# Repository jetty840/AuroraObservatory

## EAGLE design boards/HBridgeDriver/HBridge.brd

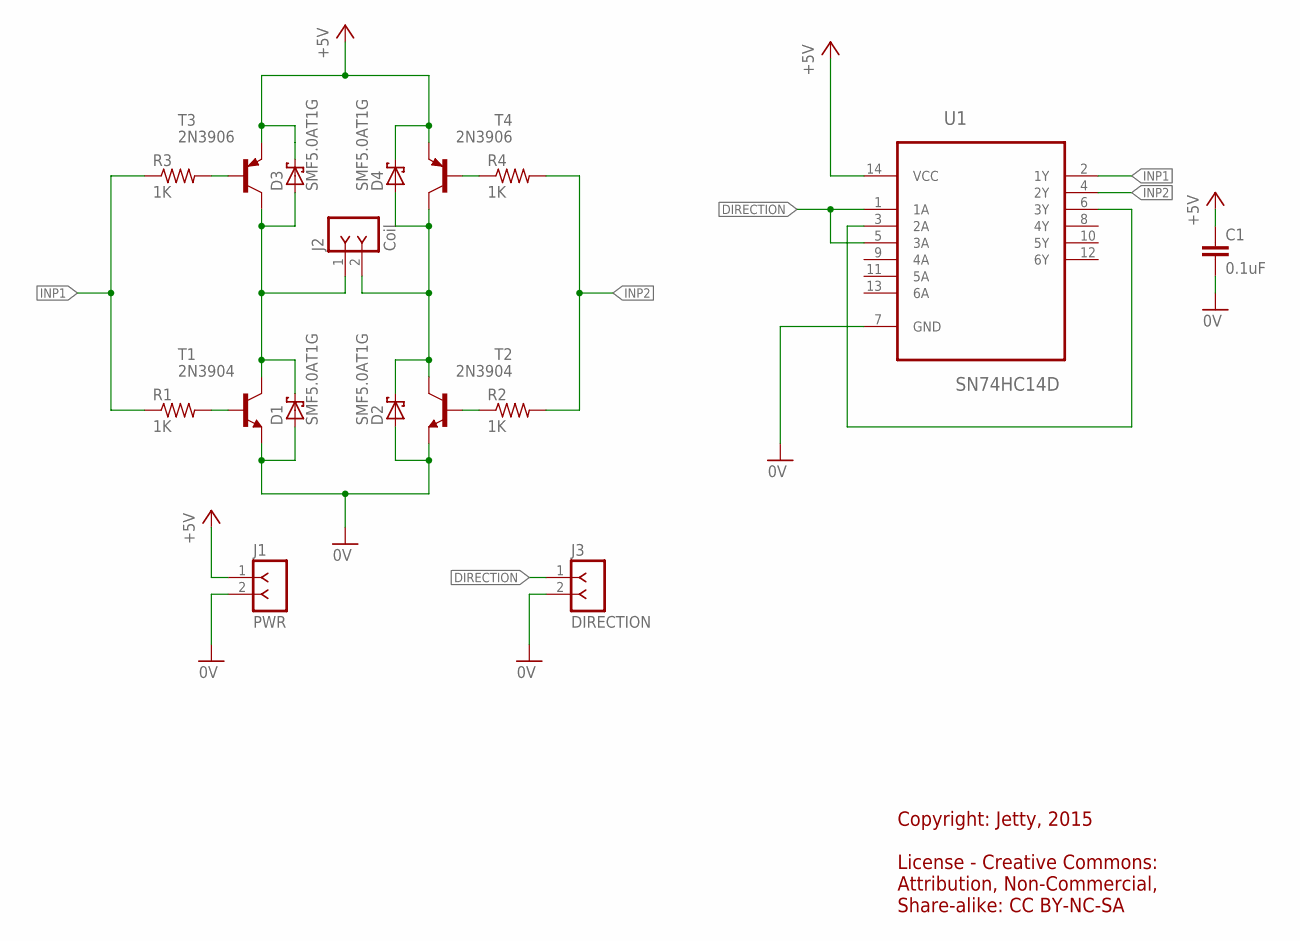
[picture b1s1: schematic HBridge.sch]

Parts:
C1: 0.1uF; C0603
D1, D2, D3, D4: SMF5.0AT1G; SOD123FL
J1: PWR; SIP-100-02-32Y
J2: Coil; SIP-100-02-32Y
J3: DIRECTION; SIP-100-02-32Y
R1, R2, R3, R4: 1K; R0603
T1, T2: 2N3904; SOT23-BEC
T3, T4: 2N3906; SOT23-BEC
U1: SN74HC14D; SOIC127P600X175-14N

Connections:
0V: C1.2, D1.A, D2.A, J1.2, J3.2, T1.E, T2.E, U1.7 (GND)
+5V: C1.1, D3.C, D4.C, J1.1, T3.E, T4.E, U1.14 (VCC)
DIRECTION: J3.1, U1.1 (1A), U1.5 (3A)
INP1: R1.1, R3.1, U1.2 (1Y)
INP2: R2.2, R4.2, U1.4 (2Y)
unnamed: R1.2, T1.B
unnamed: R2.1, T2.B
unnamed: R3.2, T3.B
unnamed: R4.1, T4.B
unnamed: D2.C, D4.A, J2.2, T2.C, T4.C
unnamed: D1.C, D3.A, J2.1, T1.C, T3.C
unnamed: U1.3 (2A), U1.6 (3Y)

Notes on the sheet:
Copyright: Jetty, 2015 License - Creative Commons: Attribution, Non-Commercial, Share-alike: CC BY-NC-SA

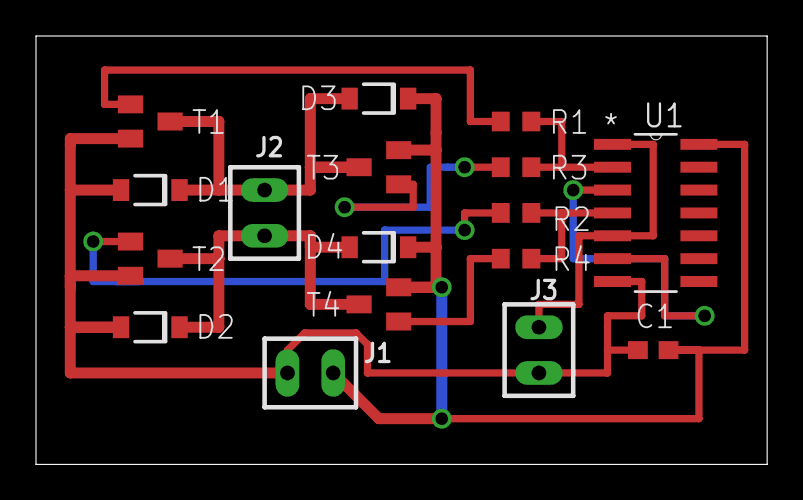
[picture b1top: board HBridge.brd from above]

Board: 2 copper layers, 40.6 x 23.8 mm, 17 parts (0 on the bottom side), 12 nets.

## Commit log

2015-08-18 Initial Commit
    Adding system design diagram and HBridge Driver (schematic / pcb)

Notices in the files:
parts and their libraries:
con-headers-jp: Copyright (C) 2008, Bob Starr
